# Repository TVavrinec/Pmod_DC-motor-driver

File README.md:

# Pmod_DC-motor-driver
Simple DC motor driver with Pmod connector for use with, for example, ELKS boards ([**ESP Learning Kit Starter**](https://github.com/RoboticsBrno/RB3206-ELKS)) or [**Logic v2**](https://github.com/RoboticsBrno/RB3205-Logic/tree/main).
This boart us [DRV8833](https://www.ti.com/lit/ds/symlink/drv8833.pdf?ts=1706616937503&ref_url=https%253A%252F%252Fwww.google.com%252F) motor driver that can drive two DC motors with a maximum continuous current of 1.5 A.

The power ENC jumper serves as an option to disconnect the 5V power supply from the motor connector for ENCs that are not 5V tolerant. In normal mode you need to connect a jumper.

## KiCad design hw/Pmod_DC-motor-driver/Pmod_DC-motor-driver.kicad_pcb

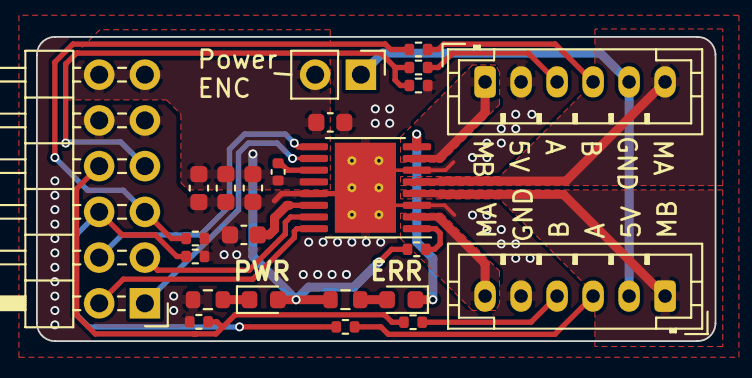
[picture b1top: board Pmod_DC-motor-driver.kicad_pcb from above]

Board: 2 copper layers, 37.7 x 16.9 mm, 24 parts (0 on the bottom side), 25 nets.

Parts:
C1, C12, C13, C14: 10u; C_0603_1608Metric
C11: 0.1u; C_0402_1005Metric
C15: 2.2uF; C_0603_1608Metric
D1, D2: LED; LED_0603_1608Metric
J1, J6: Encoder; JST_PH_B6B-PH-K_1x06_P2.00mm_Vertical
J8: Conn_02x06_Odd_Even; PinHeader_2x06_P2.54mm_Horizontal
JP4: Jumper_2_Bridged; PinHeader_1x02_P2.54mm_Vertical
R1: 470; R_0603_1608Metric
R2: 1k; R_0603_1608Metric
R3, R8, R9, R10, R24: 10k; R_0402_1005Metric
R4, R5, R6, R7: 4k7; R_0402_1005Metric
U6: DRV8833; HTSSOP-16-1EP_4.4x5mm_P0.65mm_EP3.4x5mm_Mask2.46x2.31mm_The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

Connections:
+5V: C1.1, C11.1, C12.1, C13.1, C14.1, D2.2 (A), J8.11, J8.12, JP4.2 (B), R1.1, R24.1, U6.12 (VM)
/ENC_A1: J8.6, R6.1, R9.1
/ENC_A2: J8.5, R5.1, R8.1
/ENC_B1: J8.8, R7.1, R10.1
/ENC_B2: J8.7, R3.1, R4.1
/PWM-A1: J8.2, U6.16 (AIN1)
/PWM-A2: J8.1, U6.10 (BIN2)
/PWM-B1: J8.4, U6.9 (BIN1)
/PWM-B2: J8.3, U6.15 (AIN2)
GND: C1.2, C12.2, C13.2, C14.2, C15.2, J1.2, J6.5, J8.9, J8.10, R2.2, R3.2, R8.2, R9.2, R10.2, U6.3 (AISEN), U6.6 (BISEN), U6.13 (GND), U6.17 (GND)
unnamed: D1.2 (A), R1.2
unnamed: D1.1 (K), U6.8 (nFAULT)
unnamed: D2.1 (K), R2.1
unnamed: J1.1, U6.7 (BOUT1)
unnamed: J1.3, R4.2
unnamed: J1.4, R5.2
unnamed: J1.5, J6.2, JP4.1 (A)
unnamed: J1.6, U6.5 (BOUT2)
unnamed: J6.1, U6.4 (AOUT2)
unnamed: J6.3, R6.2
unnamed: J6.4, R7.2
unnamed: J6.6, U6.2 (AOUT1)
unnamed: C11.2, U6.11 (VCP)
unnamed: C15.1, U6.14 (VINT)
unnamed: R24.2, U6.1 (nSLEEP)

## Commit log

2024-03-18 Add README
2024-03-19 Pmod label
2024-03-19 Power ENC jumper description
2024-03-19 Add divider to ENC line
